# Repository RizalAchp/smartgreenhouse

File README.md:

<h1 id="JUDUL">
    SMART GREENHOUSE WITH ARDUINO AND TELEMETRIX
</h1>
<h4>
    Automisasi pada greenhouse berupa pengukuran dan pengontrol suhu, kelembapan udara, kelembapan tanah, sirkulasi udara, serta besar cahaya pada environment yang di tentukan
</h4>

_oleh:_  
**[TIM TREESAKTI : TKK POLIJE](https://github.com/RizalAchp)**

## alat dan bahan

1. **Arduino Uno Ref3 ATMEGA328** _( module arduino )_
2. **dht11 sensor** _( sensor humadity dan suhu ruangan )_
3. **4 relays** _( coil 12 v )_
4. **kipas 12v/5v** _( kipas DC kecil )_
5. **pump 12v** _( water pump )_
6. **hcsr04** _( ultrasonic sensor )_
7. **soil moisture sensor** _( sensor kelembapan tanah )_
8. **Light Depentent Resistor** _( ldr / sensor cahaya )_
9. **supply power/regulator** _( 12v and 5v )_
10. **acrilic** _( tempat dudukan semua module )_
    <!-- 11. **12c LCD 16x2** _( lcd sebagai indikator tambahan )_ -->
    <!-- 12. **LED array** _( led sebagai indikator tambahan )_ -->

<h2 id="cara-menjalankan">
    cara menjalankan
</h2>

1. download repo ini secara manual atau clone menggunakan git

   ```bash
   git clone --recursive https://github.com/RizalAchp/smartgreenhouse.git
   cd ./smartgreenhouse
   ```

2. install dependensi

   ```bash
   pip install -r ./requirement.txt
   ```

3. buka arduino IDE, dan download Library `Telemetrix4Arduino` pada library manager dan upload Example dari library tersebut pada `Arduino Uno / Nano` minimal yang menggunakan `ATMEGA328` sebagai microcontrollernya.

4. setelah itu kembali pada directory `smartgreenhouse`, dan jalankan program dengan cara:

   ```bash
   python ./main.py
   ```

   atau jika anda berada pada linux:

   ```bash
   python3 ./main.py
   ```

5. Selesai

**untuk definisi pin yang digunakan bisa dihilhat di [DI SINI](#DEFINISI-PIN)**

<h2 id="software-yang-digunakan">
    sofware yang digunakan
</h2>

1. **vim** _( text editor )_
2. **python3** _( bahasa pemrograman yang di pakai )_

   - **Telemetrix** _( module python3 sebagai intrepeter ke arduino
     sama seperti pyfirmata namun fitur lebih banyk )_
   - **dashing** _( module python untuk menampilkan / menvisualisasikan data dalam bentuk gauge
     maupun numerik didalam terminal emulator )_

<h2 id="proses yang dilakukan">
   proses yang dilakukan
</h2>

3. membuat wadah semua module kedalam acrilic untuk mempermudah dan meminimalisir tempat maupun kerapian dalam module

4. menggunakan regulator sebagai pengatur daya agar distribusi daya stabil

5. module sensor dapat di tambah maupun di ubah dengan module sensor lain selama pin yang dibutuhkan sama

6. memrogram full dengn python
7. menvisualisasikan data kedalam TUI ( Terminal User Interface )\
   ~~data value yang didapatkan di simpan didalam database ( mysql )~~\
   <!--TODOO --> ~~memvisualisasikan kedalam web server maupun mobile app~~ ( future )

<h2 id="kelebihan">
    Kelebihan
</h2>

1. minimalis
2. full di program dengan python yang dapat mumudahkan mendeploy dan menjalankan program pada raspberry pi
3. karena data di simpan didalam daabase, memudahkan kita untuk memvisualisasikan kedalam pengaplikasiann kedepannya

<h2 id="DEFINISI-PIN">
    Definisi Pin yang digunakan pada arduino
</h2>

- **PIN ANALOG =**

  | ALAT                 |   PIN    |
  | -------------------- | :------: |
  | Sensor Soil Moisture | Analog 0 |
  | Sensor LDR           | Analog 1 |
  | i2c LCD (SDA)        | Analog 4 |
  | i2c LCD (SCL)        | Analog 5 |

- **PIN DIGITAL =**

  | ALAT             |           PIN            |
  | ---------------- | :----------------------: |
  | Sensor DHT11     |        Digital 11        |
  | Trig pin HCSR-04 |        Digital 9         |
  | Echo Pin HCSR-04 |        Digital 10        |
  | Relay            |        Digital 2         |
  | Relay            |        Digital 3         |
  | Relay            |        Digital 4         |
  | Relay            |        Digital 5         |
  | LED              | Digital 13,12,10,9,8,7,6 |

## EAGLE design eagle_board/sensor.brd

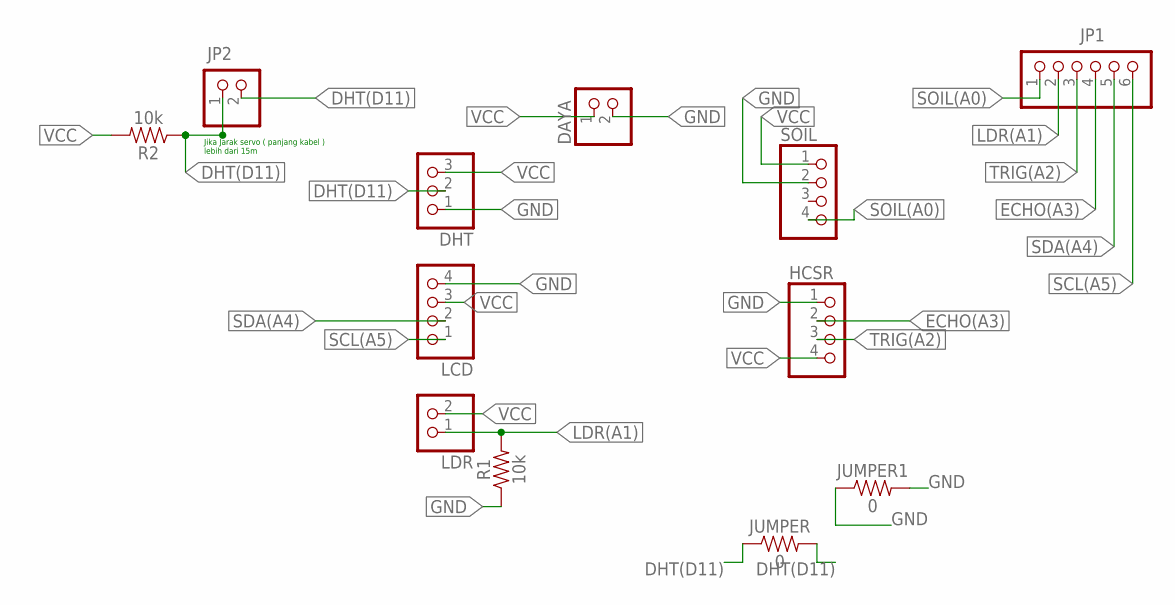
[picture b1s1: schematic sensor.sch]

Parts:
DAYA: PINHD-1X2; 1X02
DHT: PINHD-1X3; 1X03
HCSR: PINHD-1X4; 1X04
JP1: PINHD-1X6; 1X06
JP2: PINHD-1X2; 1X02
JUMPER, JUMPER1: 0; AXIAL-0.3
LCD: PINHD-1X4; 1X04
LDR: PINHD-1X2; 1X02
R1, R2: 10k; AXIAL-0.3
SOIL: PINHD-1X4; 1X04

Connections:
DHT(D11): DHT.2, JP2.1, JP2.2, JUMPER.P$1 (1), JUMPER.P$2 (2), R2.P$1 (1)
ECHO(A3): HCSR.2, JP1.4
GND: DAYA.2, DHT.1, HCSR.1, JUMPER1.P$1 (1), JUMPER1.P$2 (2), LCD.4, R1.P$1 (1), SOIL.2
LDR(A1): JP1.2, LDR.1, R1.P$2 (2)
SCL(A5): JP1.6, LCD.1
SDA(A4): JP1.5, LCD.2
SOIL(A0): JP1.1, SOIL.4
TRIG(A2): HCSR.3, JP1.3
VCC: DAYA.1, DHT.3, HCSR.4, LCD.3, LDR.2, R2.P$2 (2), SOIL.1

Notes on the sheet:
Jika Jarak servo ( panjang kabel ) lebih dari 15m

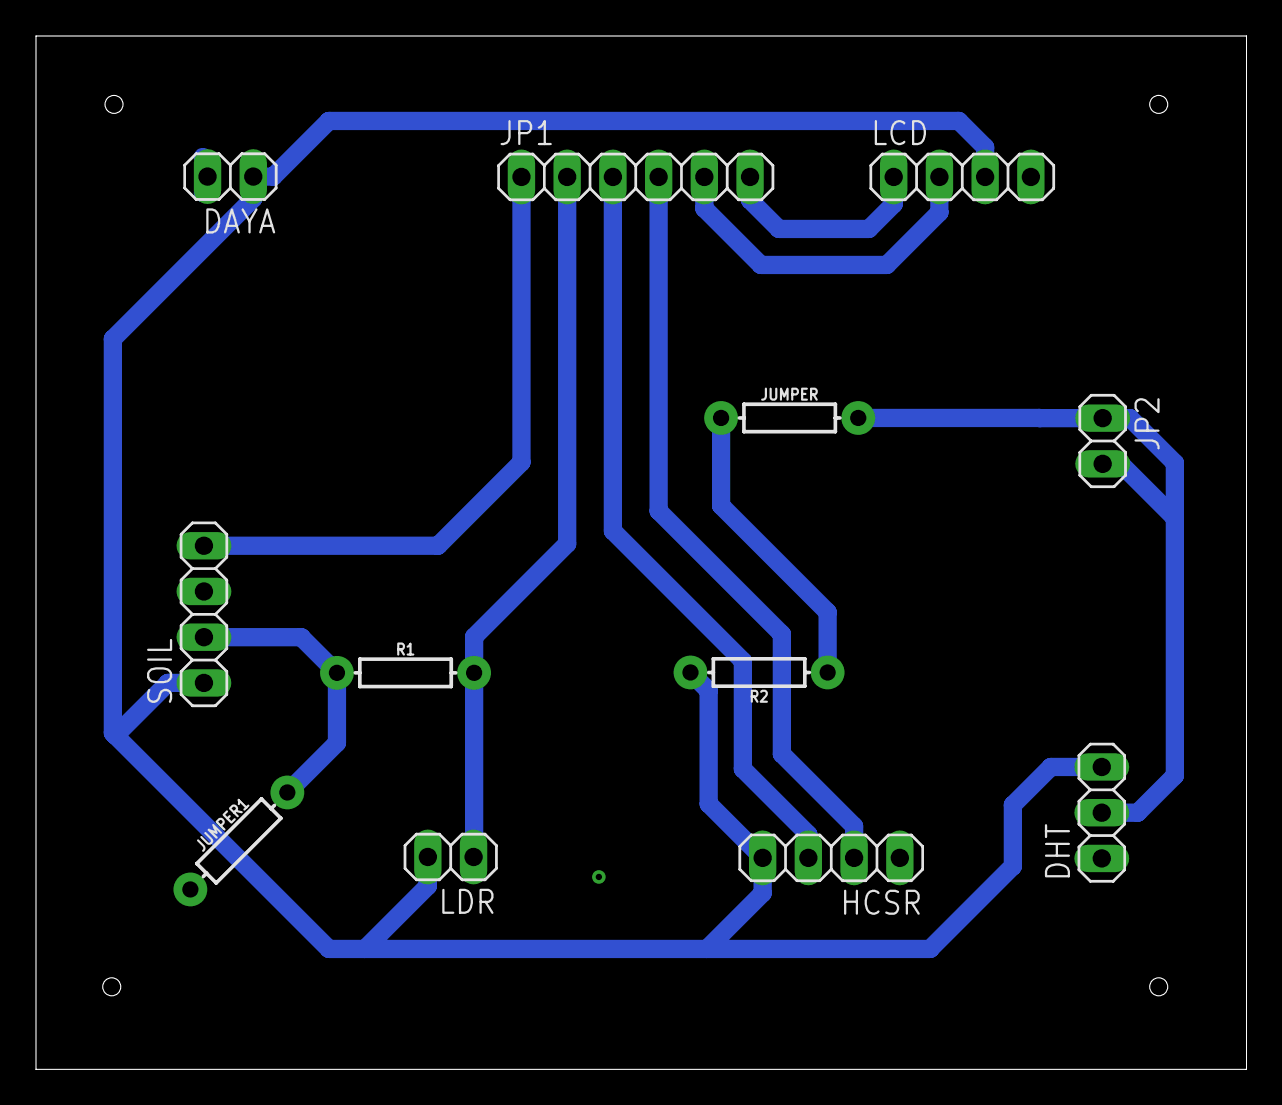
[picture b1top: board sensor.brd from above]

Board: 2 copper layers, 67.2 x 57.4 mm, 12 parts (0 on the bottom side), 9 nets.

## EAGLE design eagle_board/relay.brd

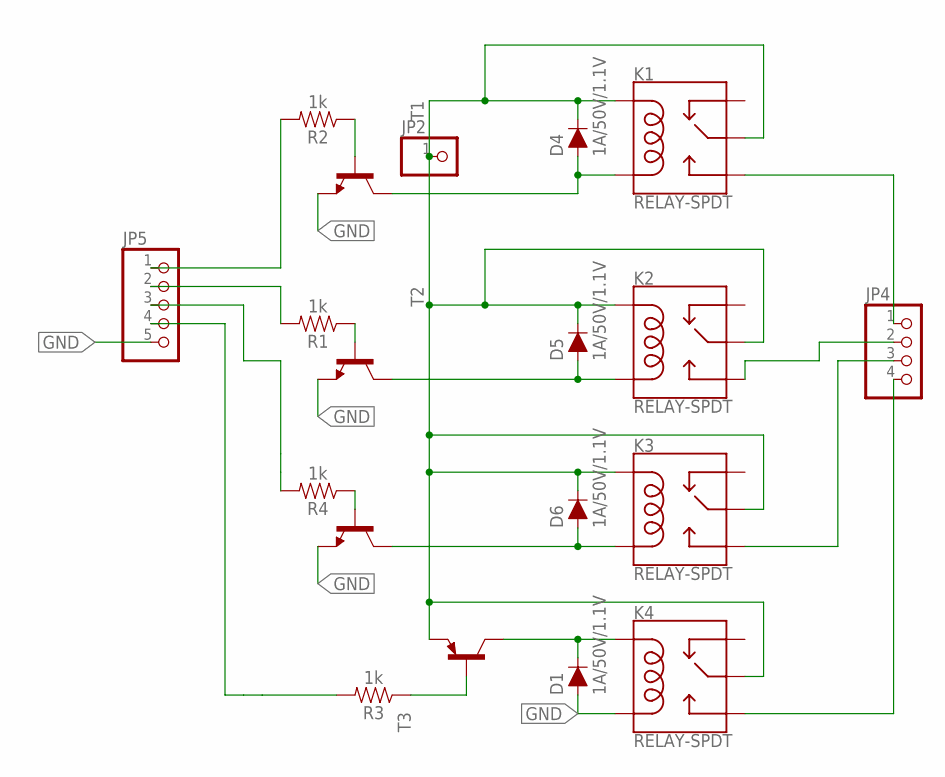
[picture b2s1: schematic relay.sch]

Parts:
D1, D4, D5, D6: 1A/50V/1.1V; DIODE-1N4001
JP2: PINHD-1X1; 1X01
JP4: PINHD-1X4; 1X04
JP5: PINHD-1X5; 1X05
K1, K2, K3, K4: RELAY-SPDT; RELAY_G5LE
R1, R2, R3, R4: 1k; AXIAL-0.3
T1, T2, T4: 2N5401-NPN-TO92-CBE; TO92-CBE
T3: 2N4126-PNP-TO92-CBE; TO92-CBE

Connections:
124: D6.A, K3.5 (COIL2), T4.C
GND: D1.A, JP5.5, K4.5 (COIL2), T1.E, T2.E, T4.E
unnamed: JP4.1, K1.3 (NO)
unnamed: JP4.2, K2.3 (NO)
unnamed: JP4.3, K3.3 (NO)
unnamed: D5.A, K2.5 (COIL2), T2.C
unnamed: D4.A, K1.5 (COIL2), T1.C
unnamed: R1.P$1 (1), T2.B
unnamed: D4.C, D5.C, D6.C, JP2.1, K1.1 (MAIN), K1.2 (COIL1), K2.1 (MAIN), K2.2 (COIL1), K3.1 (MAIN), K3.2 (COIL1), K4.1 (MAIN), T3.E
unnamed: R3.P$1 (1), T3.B
unnamed: JP5.3, R4.P$2 (2)
unnamed: JP5.2, R1.P$2 (2)
unnamed: JP5.1, R2.P$2 (2)
unnamed: R2.P$1 (1), T1.B
unnamed: JP4.4, K4.3 (NO)
unnamed: D1.C, K4.2 (COIL1), T3.C
unnamed: R4.P$1 (1), T4.B
unnamed: JP5.4, R3.P$2 (2)

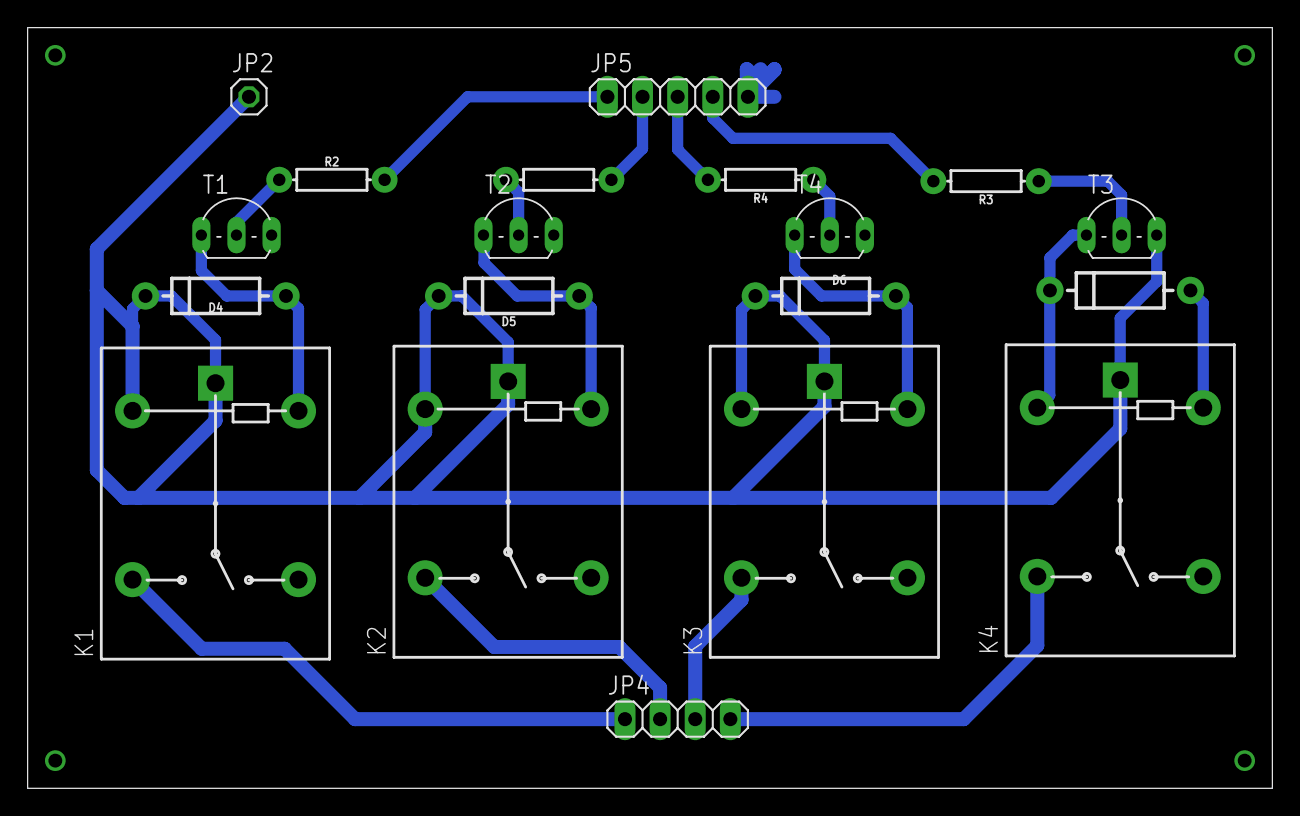
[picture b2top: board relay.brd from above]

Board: 2 copper layers, 90.0 x 55.0 mm, 19 parts (0 on the bottom side), 18 nets.

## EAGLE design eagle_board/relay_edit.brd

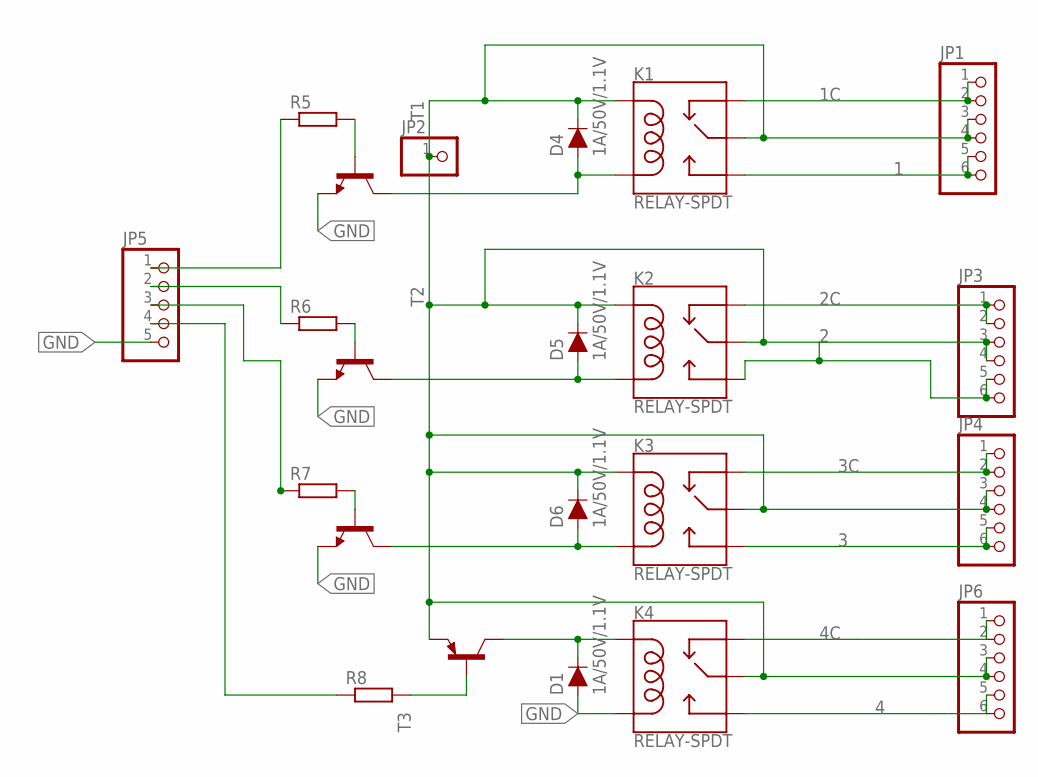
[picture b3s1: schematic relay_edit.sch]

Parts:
D1, D4, D5, D6: 1A/50V/1.1V; DIODE-1N4001
JP1, JP3, JP4, JP6: PINHD-1X6; 1X06
JP2: PINHD-1X1; 1X01
JP5: PINHD-1X5; 1X05
K1, K2, K3, K4: RELAY-SPDT; RELAY_G5LE
R5, R6, R7, R8: R-EU_0204/5; 0204/5
T1, T2, T4: 2N5401-NPN-TO92-CBE; TO92-CBE
T3: 2N4126-PNP-TO92-CBE; TO92-CBE

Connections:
1: JP1.5, JP1.6, K1.3 (NO)
1C: JP1.1, JP1.2, K1.4 (NC)
2: JP3.5, JP3.6, K2.3 (NO)
2C: JP3.1, JP3.2, K2.4 (NC)
3: JP4.5, JP4.6, K3.3 (NO)
3C: JP4.1, JP4.2, K3.4 (NC)
4: JP6.5, JP6.6, K4.3 (NO)
4C: JP6.1, JP6.2, K4.4 (NC)
124: D6.A, K3.5 (COIL2), T4.C
GND: D1.A, JP5.5, K4.5 (COIL2), T1.E, T2.E, T4.E
unnamed: D5.A, K2.5 (COIL2), T2.C
unnamed: D4.A, K1.5 (COIL2), T1.C
unnamed: R6.2, T2.B
unnamed: D4.C, D5.C, D6.C, JP1.3, JP1.4, JP2.1, JP3.3, JP3.4, JP4.3, JP4.4, JP6.3, JP6.4, K1.1 (MAIN), K1.2 (COIL1), K2.1 (MAIN), K2.2 (COIL1), K3.1 (MAIN), K3.2 (COIL1), K4.1 (MAIN), T3.E
unnamed: R8.2, T3.B
unnamed: JP5.3, R7.1
unnamed: JP5.2, R6.1
unnamed: JP5.1, R5.1
unnamed: R5.2, T1.B
unnamed: D1.C, K4.2 (COIL1), T3.C
unnamed: R7.2, T4.B
unnamed: JP5.4, R8.1

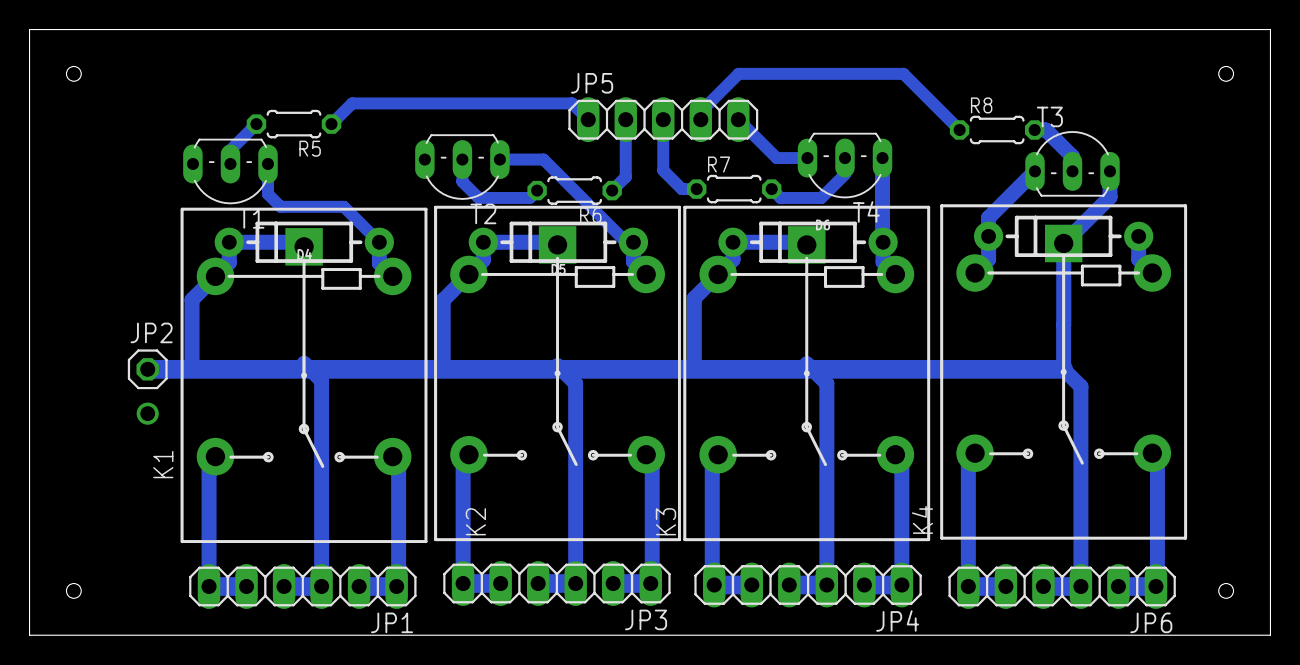
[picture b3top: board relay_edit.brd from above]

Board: 2 copper layers, 84.0 x 41.0 mm, 22 parts (0 on the bottom side), 22 nets.

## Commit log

2021-12-19 finish
2021-12-24 updating
2022-01-09 README
2022-01-10 nambah Error Handling dan mengoptimasi program
2022-01-11 mengoptimasi program

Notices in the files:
parts and their libraries:
SparkFun-Electromechanical: Licensing: Creative Commons ShareAlike 4.0 International - https://creativecommons.org/licenses/by-sa/4.0
